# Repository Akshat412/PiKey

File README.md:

# PiKey
This is a SoM (System-on-Module) for the RP2040 microcontroller from Raspberry Pi. The module is based on a 2242 M.2 B+M card (2.2 cm x 4.2 cm) and can be plugged into M.2 B or M connectors.

The module can be used for any project requiring a microcontroller, and would save a lot of time in board design and assembly as well as cost, as it implements all of the required peripherals for working with an RP2040 microcontroller. Any projects using this would just need to be carrier boards for this SoM. This was inspired by Phil's Lab, who made a similar module for an STM32, and timonsku, who made a similar module for the RP2040 and also open-sourced the M.2 card footprint for KiCad!

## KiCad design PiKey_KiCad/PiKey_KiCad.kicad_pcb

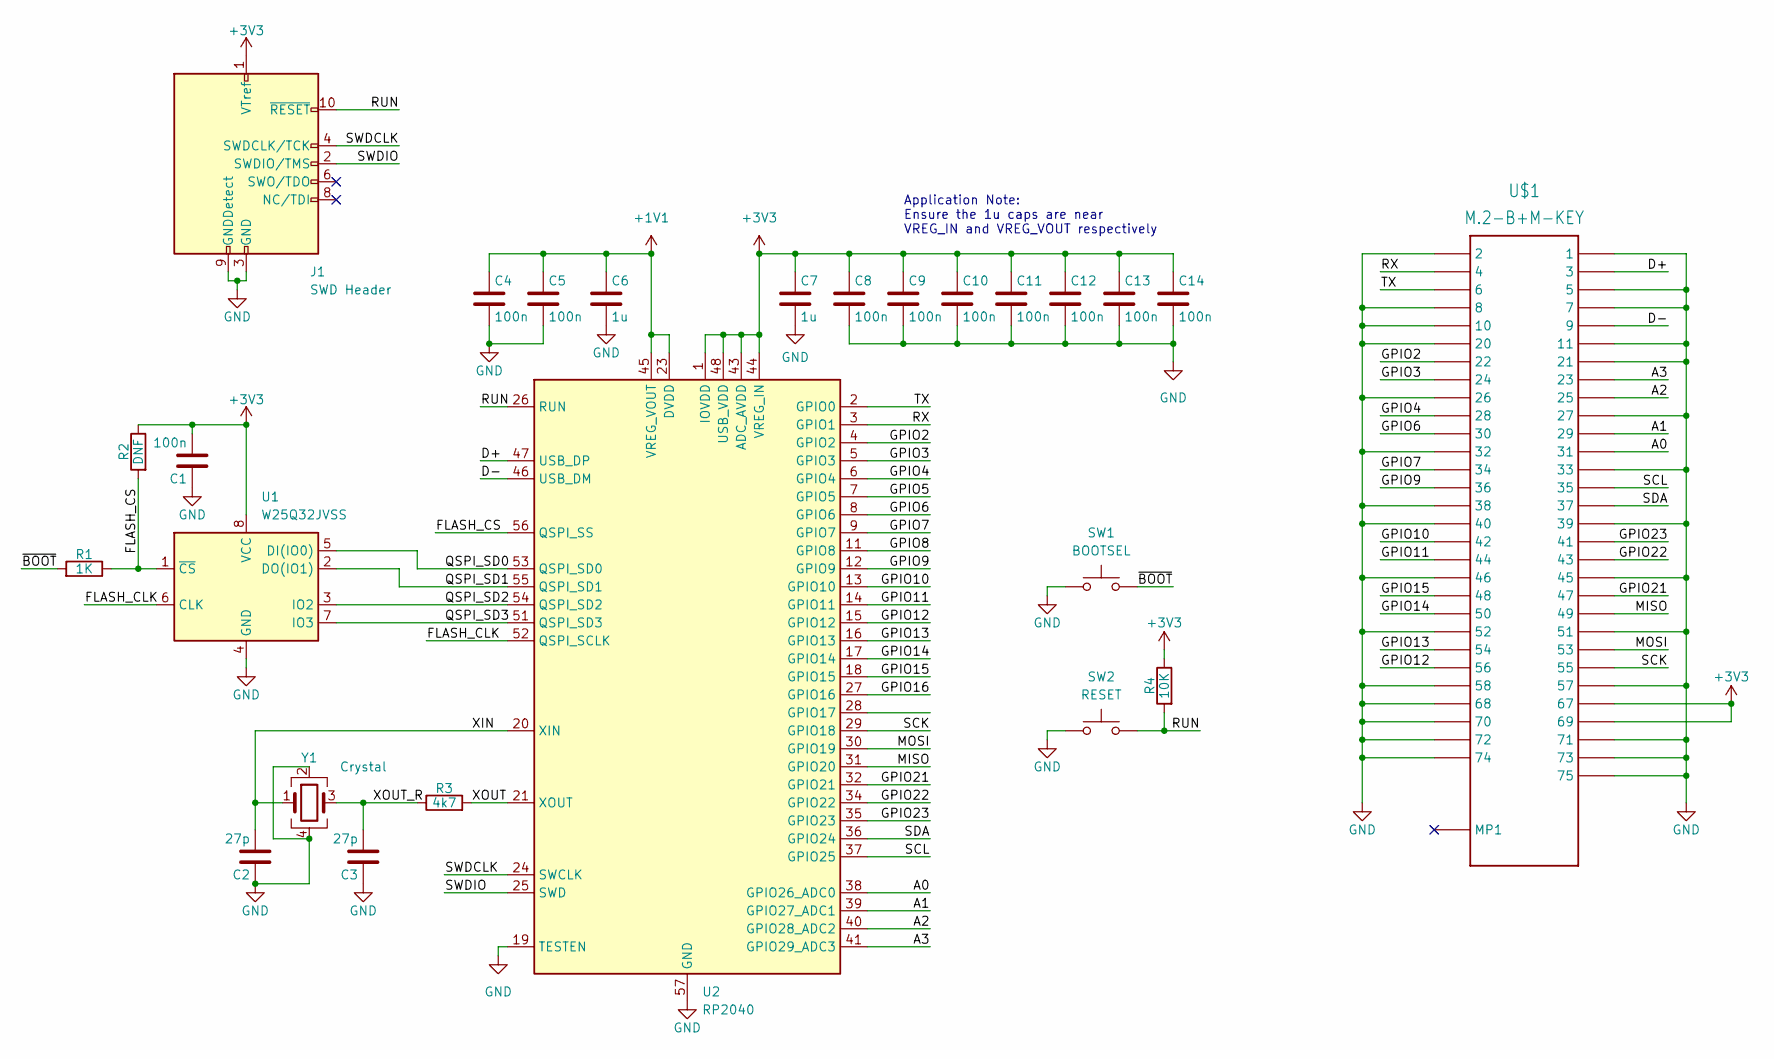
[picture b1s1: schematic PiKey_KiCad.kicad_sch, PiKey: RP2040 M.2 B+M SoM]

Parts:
C1: 100n; C_0603_1608Metric_Pad1.08x0.95mm_HandSolder
C2, C3: 27p; C_0603_1608Metric_Pad1.08x0.95mm_HandSolder
C4, C5, C8, C9, C10, C11, C12, C13, C14: 100n; C_0402_1005Metric
C6, C7: 1u; C_0402_1005Metric
J1: SWD Header; PinHeader_2x05_P1.27mm_Vertical_SMD
R1: 1K; R_0603_1608Metric_Pad0.98x0.95mm_HandSolder
R2: DNF; R_0603_1608Metric_Pad0.98x0.95mm_HandSolder
R3: 4k7; R_0603_1608Metric_Pad0.98x0.95mm_HandSolder
R4: 10K; R_0603_1608Metric_Pad0.98x0.95mm_HandSolder
SW1: BOOTSEL; SW_Push_1P1T_NO_CK_KMR2
SW2: RESET; SW_Push_1P1T_NO_CK_KMR2
U1: W25Q32JVSS; SOIC-8_5.23x5.23mm_P1.27mm
U2: RP2040; QFN-56-1EP_7x7mm_P0.4mm_EP3.2x3.2mm
U$1: M.2-B+M-KEY
Y1: Crystal; Crystal_SMD_SeikoEpson_FA238-4Pin_3.2x2.5mm

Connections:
+1V1: C4.1, C5.1, C6.1, U2.23 (DVDD), U2.45 (VREG_VOUT), U2.50 (DVDD)
+3V3: C1.2, C7.1, C8.1, C9.1, C10.1, C11.1, C12.1, C13.1, C14.1, J1.1 (VTref), R2.1, R4.1, U1.8 (VCC), U2.1 (IOVDD), U2.10 (IOVDD), U2.22 (IOVDD), U2.33 (IOVDD), U2.42 (IOVDD), U2.43 (ADC_AVDD), U2.44 (VREG_IN), U2.48 (USB_VDD), U2.49 (IOVDD), U$1.P$67 (67), U$1.P$69 (69)
/A0: U2.38 (GPIO26_ADC0), U$1.P$31 (31)
/A1: U2.39 (GPIO27_ADC1), U$1.P$29 (29)
/A2: U2.40 (GPIO28_ADC2), U$1.P$25 (25)
/A3: U2.41 (GPIO29_ADC3), U$1.P$23 (23)
/D+: U2.47 (USB_DP), U$1.P$3 (3)
/D-: U2.46 (USB_DM), U$1.P$9 (9)
/FLASH_CLK: U1.6 (CLK), U2.52 (QSPI_SCLK)
/FLASH_CS: R1.1, R2.2, U1.1 (~CS), U2.56 (QSPI_SS)
/GPIO2: U2.4 (GPIO2), U$1.P$22 (22)
/GPIO3: U2.5 (GPIO3), U$1.P$24 (24)
/GPIO4: U2.6 (GPIO4), U$1.P$28 (28)
/GPIO5: U2.7 (GPIO5)
/GPIO6: U2.8 (GPIO6), U$1.P$30 (30)
/GPIO7: U2.9 (GPIO7), U$1.P$34 (34)
/GPIO8: U2.11 (GPIO8)
/GPIO9: U2.12 (GPIO9), U$1.P$36 (36)
/GPIO10: U2.13 (GPIO10), U$1.P$42 (42)
/GPIO11: U2.14 (GPIO11), U$1.P$44 (44)
/GPIO12: U2.15 (GPIO12), U$1.P$56 (56)
/GPIO13: U2.16 (GPIO13), U$1.P$54 (54)
/GPIO14: U2.17 (GPIO14), U$1.P$50 (50)
/GPIO15: U2.18 (GPIO15), U$1.P$48 (48)
/GPIO16: U2.27 (GPIO16)
/GPIO21: U2.32 (GPIO21), U$1.P$47 (47)
/GPIO22: U2.34 (GPIO22), U$1.P$43 (43)
/GPIO23: U2.35 (GPIO23), U$1.P$41 (41)
/MISO: U2.31 (GPIO20), U$1.P$49 (49)
/MOSI: U2.30 (GPIO19), U$1.P$53 (53)
/QSPI_SD0: U1.5 (DI(IO0)), U2.53 (QSPI_SD0)
/QSPI_SD1: U1.2 (DO(IO1)), U2.55 (QSPI_SD1)
/QSPI_SD2: U1.3 (IO2), U2.54 (QSPI_SD2)
/QSPI_SD3: U1.7 (IO3), U2.51 (QSPI_SD3)
/RUN: J1.10 (~RESET), R4.2, SW2.2, U2.26 (RUN)
/RX: U2.3 (GPIO1), U$1.P$4 (4)
/SCK: U2.29 (GPIO18), U$1.P$55 (55)
/SCL: U2.37 (GPIO25), U$1.P$35 (35)
/SDA: U2.36 (GPIO24), U$1.P$37 (37)
/SWDCLK: J1.4 (SWDCLK/TCK), U2.24 (SWCLK)
/SWDIO: J1.2 (SWDIO/TMS), U2.25 (SWD)
/TX: U2.2 (GPIO0), U$1.P$6 (6)
/XIN: C2.2, U2.20 (XIN), Y1.1
/XOUT: R3.2, U2.21 (XOUT)
/XOUT_R: C3.2, R3.1, Y1.3
/~BOOT: R1.2, SW1.2
GND: C1.1, C2.1, C3.1, C4.2, C5.2, C6.2, C7.2, C8.2, C9.2, C10.2, C11.2, C12.2, C13.2, C14.2, J1.3 (GND), J1.5 (GND), J1.9 (GNDDetect), SW1.1, SW2.1, U1.4 (GND), U2.19 (TESTEN), U2.57 (GND), U$1.P$1 (1), U$1.P$2 (2), U$1.P$5 (5), U$1.P$7 (7), U$1.P$8 (8), U$1.P$10 (10), U$1.P$11 (11), U$1.P$20 (20), U$1.P$21 (21), U$1.P$26 (26), U$1.P$27 (27), U$1.P$32 (32), U$1.P$33 (33), U$1.P$38 (38), U$1.P$39 (39), U$1.P$40 (40), U$1.P$45 (45), U$1.P$46 (46), U$1.P$51 (51), U$1.P$52 (52), U$1.P$57 (57), U$1.P$58 (58), U$1.P$68 (68), U$1.P$70 (70), U$1.P$71 (71), U$1.P$72 (72), U$1.P$73 (73), U$1.P$74 (74), U$1.P$75 (75), Y1.2, Y1.4

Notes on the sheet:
Application Note: Ensure the 1u caps are near VREG_IN and VREG_VOUT respectively

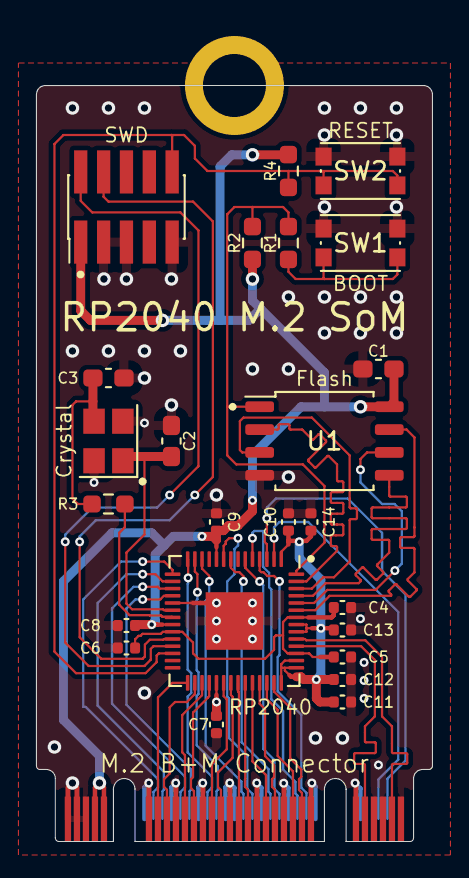
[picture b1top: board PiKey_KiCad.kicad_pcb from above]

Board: 4 copper layers, 22.0 x 42.0 mm, 25 parts (0 on the bottom side), 44 nets.

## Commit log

2023-06-15 Added M.2 Connector and RP2040
2023-06-27 Initial routing
    Need to finish routing power and connecting GNDs together.
2023-07-15 Delay matching and stitching vias
2023-07-27 Redid M.2 signals on back
2023-09-03 Improved silkscreen
2023-09-11 PR revision 2
    Fixed 3D model of board, added test points
2023-09-15 Fixed page settings, added BOM
